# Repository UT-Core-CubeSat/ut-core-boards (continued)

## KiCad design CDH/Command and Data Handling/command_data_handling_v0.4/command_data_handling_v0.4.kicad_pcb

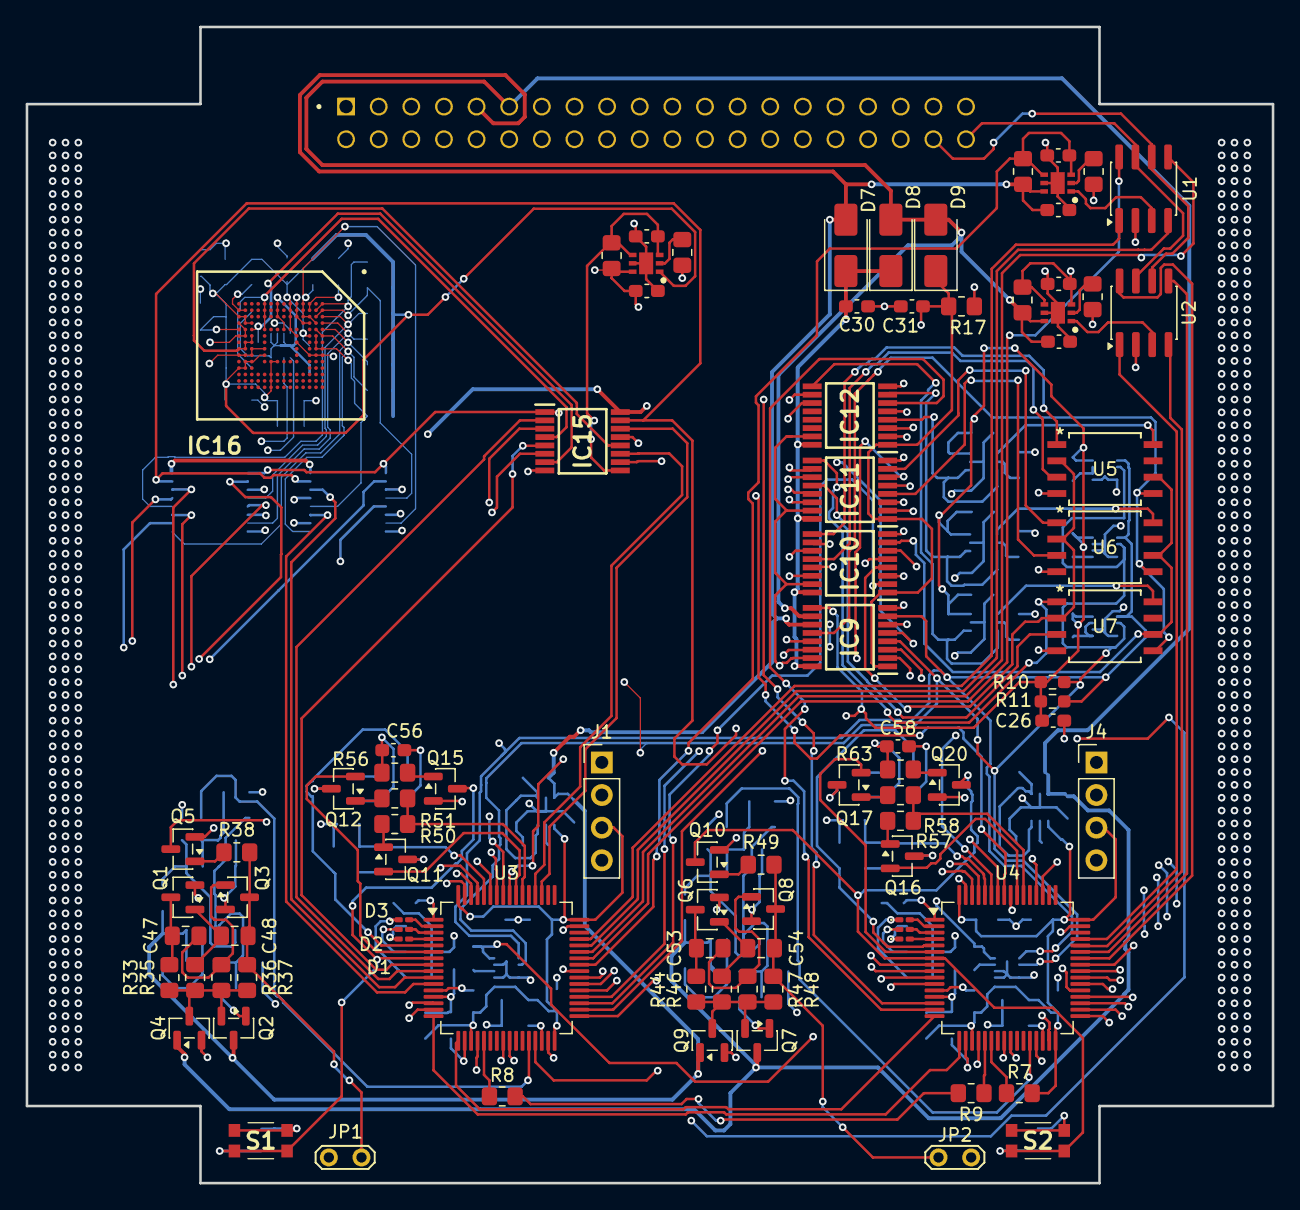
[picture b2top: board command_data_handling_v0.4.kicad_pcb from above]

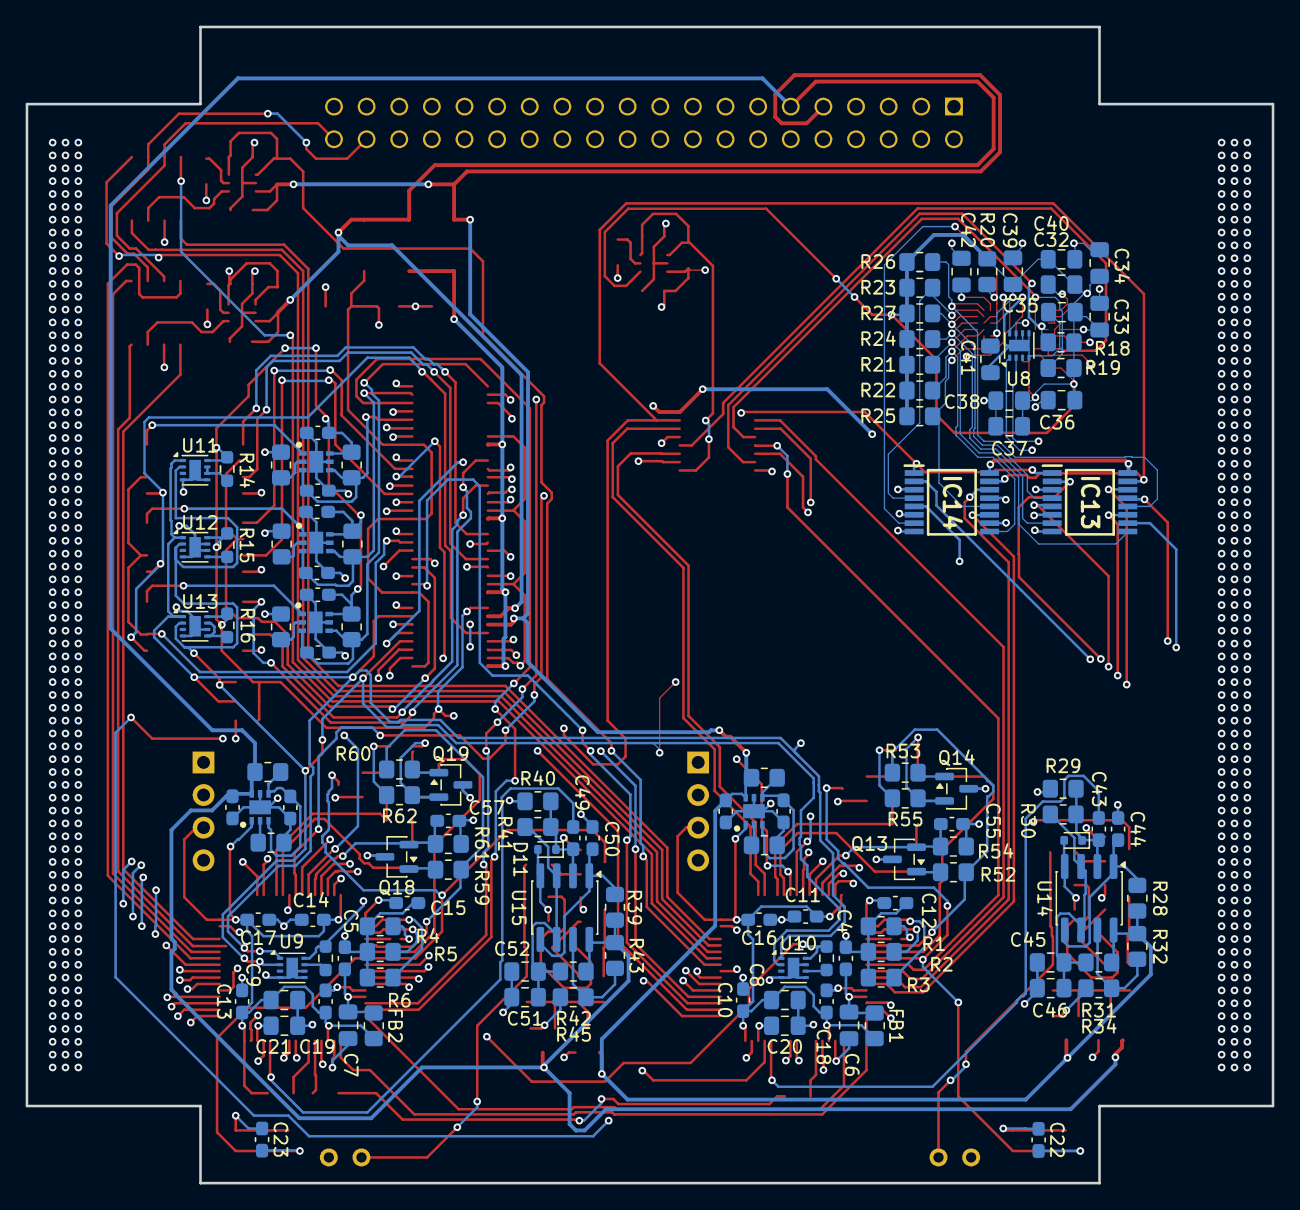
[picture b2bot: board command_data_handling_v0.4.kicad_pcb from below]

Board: 4 copper layers, 97.0 x 90.0 mm, 216 parts (125 on the bottom side), 196 nets.

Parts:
C1, C1_RETRY1, C2, C2_RETRY1, C3, C3_RETRY1, C4_RETRY1, C5_RETRY1, C6_RETRY1, C7_RETRY1, C7_RETRY2, C22, C23, C24, C25, C26, C27, C28, C29, C30, C31: 0.1µF; C_0603_1608Metric_Pad1.08x0.95mm_HandSolder
C4, C5, C10, C13, C16, C17, C18, C19, C43, C44, C49, C50: 100nF; C_0603_1608Metric_Pad1.08x0.95mm_HandSolder
C6, C7: 1µF; C_0805_2012Metric_Pad1.18x1.45mm_HandSolder
C8, C9: 10µF; C_0805_2012Metric_Pad1.18x1.45mm_HandSolder
C11, C12, C14, C15: 0.1μF; C_0603_1608Metric_Pad1.08x0.95mm_HandSolder
C20, C21, C32, C33, C34, C35, C36, C37, C38, C39, C40, C41, C42: 4.7µF; C_0805_2012Metric_Pad1.18x1.45mm_HandSolder
C45, C46, C51, C52: 10uF; C_0805_2012Metric_Pad1.18x1.45mm_HandSolder
C47, C48, C53, C54: 4.7uF; C_0805_2012Metric_Pad1.18x1.45mm_HandSolder
C55, C56, C57, C58: 0.1uF; C_0603_1608Metric_Pad1.08x0.95mm_HandSolder
D1, D2, D3, D4, D5, D6: LED; LED_0201_0603Metric_Pad0.64x0.40mm_HandSolder
D7, D8, D9: SS14; D_SMA
D10, D11: 1N4148; D_SOD-523
FB1, FB2: FerriteBead_Small; R_0805_2012Metric_Pad1.20x1.40mm_HandSolder
IC1, IC2, IC3, IC4, IC5, IC6, IC7, IC8: TPS2552DRVT-1
IC9, IC10, IC11, IC12, IC13, IC14, IC15: TMUX1574PWR
IC16: IS22EF08GP-JCLA2
J1, J4: SWD; PinHeader_1x04_P2.54mm_Vertical
J1#2: IPS1-120-01-L-D-RA
JP1, JP2: Jumper_2_Open; TestPoint_2Pads_Pitch2.54mm_Drill0.8mm
Q1, Q2, Q3, Q4, Q5, Q6, Q7, Q8, Q9, Q10, Q13, Q14, Q15, Q18, Q19, Q20: MMBT2222A; SOT-23
Q11, Q12, Q16, Q17: MMBTA94; SOT-23
R1, R2, R3, R4, R5, R6: 470Ω; R_0805_2012Metric_Pad1.20x1.40mm_HandSolder
R1_FAULT1, R2_FAULT1, R3_FAULT1, R4_FAULT1, R5_FAULT1, R6_FAULT1, R7_FAULT1, R7_FAULT2: 102kΩ; R_0805_2012Metric_Pad1.20x1.40mm_HandSolder
R1_ILIM1, R2_ILIM1, R3_ILIM1, R4_ILIM1: 88.7kΩ; R_0805_2012Metric_Pad1.20x1.40mm_HandSolder
R5_ILIM1, R6_ILIM1, R7_ILIM2: 226kΩ; R_0805_2012Metric_Pad1.20x1.40mm_HandSolder
R7, R8, R9, R33, R34, R37, R44, R45, R48: 1kΩ; R_0805_2012Metric_Pad1.20x1.40mm_HandSolder
R7_ILIM1: 108kΩ; R_0805_2012Metric_Pad1.20x1.40mm_HandSolder
R10, R11, R12, R13, R14, R15, R16: 5kΩ; R_0603_1608Metric_Pad0.98x0.95mm_HandSolder
R17, R28, R36, R38, R39, R47, R49, R56, R63: 100kΩ; R_0805_2012Metric_Pad1.20x1.40mm_HandSolder
R18: 4.7kΩ; R_0805_2012Metric_Pad1.20x1.40mm_HandSolder
R19, R29, R30, R31, R40, R41, R42, R50, R51, R52, R53, R57, R58, R59, R60: 10kΩ; R_0805_2012Metric_Pad1.20x1.40mm_HandSolder
R20, R21, R22, R23, R24, R25, R26, R27: 22.1kΩ; R_0805_2012Metric_Pad1.20x1.40mm_HandSolder
R32, R43, R54, R55, R61, R62: 5kΩ; R_0805_2012Metric_Pad1.20x1.40mm_HandSolder
R35, R46: 750kΩ; R_0805_2012Metric_Pad1.20x1.40mm_HandSolder
S1, S2: RESET; KMR731NGLFS
U1, U2: TCAN330; SOIC-8_3.9x4.9mm_P1.27mm
U3, U4: STM32U5A5RJTx; LQFP-64_10x10mm_P0.5mm
U5, U6, U7: CY15B104QN-50SXI
U8, U9, U10, U11, U12, U13: TMP1075DSG; WSON-8-1EP_2x2mm_P0.5mm_EP0.9x1.6mm
U14, U15: LM393; SOIC-8_3.9x4.9mm_P1.27mm

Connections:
/AND_Lock1/LCK1_1: R57.1, R58.1, U4.54 (PD2)
/AND_Lock1/LCK1_2: R59.2, R60.2, U4.5 (PH0)
/AND_Lock1/LCK1_OUT: C57.1, Q18.2 (E), R61.1, U4.60 (PH3)
/AND_Lock1/LCK2_IN: Q17.2 (E), U4.6 (PH1)
/AND_Lock/LCK1_1: R50.1, R51.1, U3.54 (PD2)
/AND_Lock/LCK1_2: R52.2, R53.2, U3.5 (PH0)
/AND_Lock/LCK1_OUT: C55.1, Q13.2 (E), R54.1, U3.60 (PH3)
/AND_Lock/LCK2_IN: Q12.2 (E), U3.6 (PH1)
/CANH: J1#2.40, U1.7 (CANH), U2.7 (CANH)
/CANL: J1#2.38, U1.6 (CANL), U2.6 (CANL)
/CDH1_3V3: C1.1, C24.1, D7.2 (A), IC2.6 (IN), IC4.6 (IN), IC9.11 (S3A), J1#2.09, Q2.3 (C), Q9.1 (B), R1_FAULT1.1, R2_FAULT1.2, R28.1, R31.2, R32.1, U14.8 (V+)
/CDH2_3V3: C2.1, C25.1, D8.2 (A), D9.2 (A), IC3.6 (IN), IC5.6 (IN), IC9.10 (S3B), J1#2.11, Q4.1 (B), Q7.3 (C), R3_FAULT1.1, R4_FAULT1.2, R39.1, R42.2, R43.1, U15.8 (V+)
/CLK: IC15.12 (D4), IC16.M6 (CLK), IC16.M7 (NC_81), IC16.N7 (NC_92), IC16.N8 (NC_93), IC16.P8 (NC_102)
/CMD: IC15.7 (D2), IC16.M5 (CMD), R18.1
/CS1: IC10.9 (D3), U5.1 (*CS)
/CS2: IC11.7 (D2), U6.1 (*CS)
/CS3: IC11.9 (D3), U7.1 (*CS)
/DAT0: IC13.4 (D1), IC16.A3 (DAT0), R27.1
/DAT1: IC13.7 (D2), IC16.A4 (DAT1), R24.1
/DAT2: IC13.9 (D3), IC16.A5 (DAT2), R21.1
/DAT3: IC13.12 (D4), IC16.A1 (NC_1), IC16.B2 (DAT3), R26.1
/DAT4: IC14.4 (D1), IC16.A2 (NC_2), IC16.B3 (DAT4), R23.1
/DAT5: IC14.7 (D2), IC16.B4 (DAT5), IC16.C3 (NC_20), IC16.D1 (NC_30), IC16.D2 (NC_31), IC16.D3 (NC_32), R20.1
/DAT6: IC14.9 (D3), IC16.A6 (VSS_1), IC16.B5 (DAT6), R22.1
/DAT7: IC14.12 (D4), IC16.A8 (NC_3), IC16.B6 (DAT7), IC16.B7 (NC_11), IC16.B8 (NC_12), R25.2
/EMMC_F: C7_RETRY1.1, IC1.3 (~FAULT), IC1.4 (EN), IC15.9 (D3), R7_FAULT1.1
/EMMC_VCC: C32.2, C33.2, C34.1, C35.2, C36.2, C37.2, C38.2, C39.2, C40.2, C41.2, IC1.1 (OUT), IC16.C6 (VCCQ_1), IC16.E6 (VCC_1), IC16.F1 (NC_43), IC16.F2 (NC_44), IC16.F3 (NC_45), IC16.F5 (VCC_2), IC16.H10 (VSS_4), IC16.J10 (VCC_3), IC16.J12 (NC_63), IC16.J13 (NC_64), IC16.J14 (NC_65), IC16.K9 (VCC_4), IC16.M4 (VCCQ_2), IC16.M10 (NC_84), IC16.N3 (NC_90), IC16.N4 (VCCQ_3), IC16.N10 (NC_95), IC16.N11 (NC_96), IC16.P3 (VCCQ_4), IC16.P5 (VCCQ_5), IC16.P11 (NC_104), R18.2, R19.2, R20.2, R21.2, R22.2, R23.2, R24.2, R25.1, R26.2, R27.2
/FRAM1_F: C5_RETRY1.1, IC6.3 (~FAULT), IC6.4 (EN), IC12.4 (D1), R5_FAULT1.1
/FRAM2_F: C6_RETRY1.1, IC7.3 (~FAULT), IC7.4 (EN), IC12.7 (D2), R6_FAULT1.1
/FRAM3_F: C7_RETRY2.1, IC8.3 (~FAULT), IC8.4 (EN), IC12.9 (D3), R7_FAULT2.1
/IC_I2C_SCL: IC9.4 (D1), R10.2, U8.2 (SCL), U9.2 (SCL), U10.2 (SCL), U11.2 (SCL), U12.2 (SCL), U13.2 (SCL)
/IC_I2C_SDA: IC9.7 (D2), R11.2, U8.1 (SDA), U9.1 (SDA), U10.1 (SDA), U11.1 (SDA), U12.1 (SDA), U13.1 (SDA)
/IC_SCK: IC10.7 (D2), U5.6 (SCK), U6.6 (SCK), U7.6 (SCK)
/IC_SI: IC9.12 (D4), U5.5 (SI), U6.5 (SI), U7.5 (SI)
/IC_SO: IC10.4 (D1), U5.2 (SO), U6.2 (SO), U7.2 (SO)
/MCU1_B0: Q11.2 (E), U3.55 (PB3)
/MCU1_CLK: IC15.14 (S4A), U3.51 (PC10)
/MCU1_CMD: IC15.5 (S2A), U3.8 (PC0)
/MCU1_CS1: IC10.11 (S3A), U3.29 (PB10)
/MCU1_CS2: IC11.5 (S2A), U3.61 (PB8)
/MCU1_CS3: IC11.11 (S3A), U3.56 (PB4)
/MCU1_DAT0: IC13.2 (S1A), U3.40 (PC9)
/MCU1_DAT1: IC13.5 (S2A), U3.39 (PC8)
/MCU1_DAT2: IC13.11 (S3A), U3.38 (PC7)
/MCU1_DAT3: IC13.14 (S4A), U3.37 (PC6)
/MCU1_DAT4: IC14.2 (S1A), U3.25 (PC5)
/MCU1_DAT5: IC14.5 (S2A), U3.24 (PC4)
/MCU1_DAT6: IC14.11 (S3A), U3.11 (PC3)
/MCU1_DAT7: IC14.14 (S4A), U3.10 (PC2)
/MCU1_EMMC_F: IC15.11 (S3A), U3.52 (PC11)
/MCU1_FRAM1_F: IC12.2 (S1A), U3.20 (PA4)
/MCU1_FRAM2_F: IC12.5 (S2A), U3.15 (PA1)
/MCU1_FRAM3_F: IC12.11 (S3A), U3.14 (PA0)
/MCU1_I2C1_SCL: IC9.2 (S1A), U3.58 (PB6)
/MCU1_I2C1_SDA: IC9.5 (S2A), U3.59 (PB7)
/MCU1_RST_N: IC15.2 (S1A), U3.9 (PC1)
/MCU1_SPI2_MISO: IC10.2 (S1A), U3.35 (PB14)
/MCU1_SPI2_MOSI: IC9.14 (S4A), U3.36 (PB15)
/MCU1_SPI2_SCK: IC10.5 (S2A), U3.34 (PB13)
/MCU1_WD: C43.1, U3.28 (PB2)
/MCU1_WP1: IC10.14 (S4A), U3.33 (PB12)
/MCU1_WP2: IC11.2 (S1A), U3.62 (PB9)
/MCU1_WP3: IC11.14 (S4A), U3.57 (PB5)
/MCU2_B0: Q16.2 (E), U4.55 (PB3)
/MCU2_CLK: IC15.13 (S4B), U4.51 (PC10)
/MCU2_CMD: IC15.6 (S2B), U4.8 (PC0)
/MCU2_CS1: IC10.10 (S3B), U4.29 (PB10)
/MCU2_CS2: IC11.6 (S2B), U4.61 (PB8)
/MCU2_CS3: IC11.10 (S3B), U4.56 (PB4)
/MCU2_DAT0: IC13.3 (S1B), U4.40 (PC9)
/MCU2_DAT1: IC13.6 (S2B), U4.39 (PC8)
/MCU2_DAT2: IC13.10 (S3B), U4.38 (PC7)
/MCU2_DAT3: IC13.13 (S4B), U4.37 (PC6)
/MCU2_DAT4: IC14.3 (S1B), U4.25 (PC5)
/MCU2_DAT5: IC14.6 (S2B), U4.24 (PC4)
/MCU2_DAT6: IC14.10 (S3B), U4.11 (PC3)
/MCU2_DAT7: IC14.13 (S4B), U4.10 (PC2)
/MCU2_EMMC_F: IC15.10 (S3B), U4.52 (PC11)
/MCU2_FRAM1_F: IC12.3 (S1B), U4.20 (PA4)
/MCU2_FRAM2_F: IC12.6 (S2B), U4.15 (PA1)
/MCU2_FRAM3_F: IC12.10 (S3B), U4.14 (PA0)
/MCU2_I2C1_SCL: IC9.3 (S1B), U4.58 (PB6)
/MCU2_I2C1_SDA: IC9.6 (S2B), U4.59 (PB7)
/MCU2_RST_N: IC15.3 (S1B), U4.9 (PC1)
/MCU2_SPI2_MISO: IC10.3 (S1B), U4.35 (PB14)
/MCU2_SPI2_MOSI: IC9.13 (S4B), U4.36 (PB15)
/MCU2_SPI2_SCK: IC10.6 (S2B), U4.34 (PB13)
/MCU2_WD: C49.1, U4.28 (PB2)
/MCU2_WP1: IC10.13 (S4B), U4.33 (PB12)
/MCU2_WP2: IC11.3 (S1B), U4.62 (PB9)
/MCU2_WP3: IC11.13 (S4B), U4.57 (PB5)
/MCU_MR: IC9.15 (~EN), IC10.15 (~EN), IC11.15 (~EN), IC12.15 (~EN), IC13.15 (~EN), IC14.15 (~EN), IC15.15 (~EN), R8.2, R9.2
/MUX_3V3: C3.1, C26.1, C27.1, C28.1, C29.1, IC1.6 (IN), IC6.6 (IN), IC7.6 (IN), IC8.6 (IN), IC9.9 (D3), R5_FAULT1.2, R6_FAULT1.2, R7_FAULT1.2, R7_FAULT2.2, R10.1, R11.1, R12.2, R13.2, R14.2, R15.2, R16.2, U8.8 (V+), U9.8 (V+), U10.8 (V+), U11.8 (V+), U12.8 (V+), U13.8 (V+)
/MUX_SEL: C31.2, D9.1 (K), IC9.1 (SEL), IC10.1 (SEL), IC11.1 (SEL), IC12.1 (SEL), IC13.1 (SEL), IC14.1 (SEL), IC15.1 (SEL), R17.2
/NRST1: C22.2, Q5.3 (C), Q15.3 (C), S1.1 (NO_1), S1.2 (NO_2), U3.7 (NRST)
/NRST2: C23.2, Q10.3 (C), Q20.3 (C), S2.1 (NO_1), S2.2 (NO_2), U4.7 (NRST)
/RST_N: IC15.4 (D1), IC16.K1 (NC_66), IC16.K2 (NC_67), IC16.K3 (NC_68), IC16.K5 (RST_N), R19.1
/USART2_1: U3.16 (PA2), U4.17 (PA3)
/USART2_2: U3.17 (PA3), U4.16 (PA2)
/VCC_MUX: C30.2, D7.1 (K), D8.1 (K), IC9.16 (VDD), IC10.16 (VDD), IC11.16 (VDD), IC12.16 (VDD), IC13.16 (VDD), IC14.16 (VDD), IC15.16 (VDD)
/VREF1: C8.1, C10.1, C11.1, C16.2, C18.1, FB1.2, IC2.1 (OUT), J1.3, U3.19 (VDD), U3.32 (VDD), U3.48 (VDDUSB), U3.64 (VDD)
/VREF2: C9.1, C13.1, C14.1, C17.2, C19.1, FB2.2, IC3.1 (OUT), J4.3, R7.2, U4.19 (VDD), U4.32 (VDD), U4.48 (VDDUSB), U4.64 (VDD)
/WP1: IC10.12 (D4), U5.3 (*WP)
/WP2: IC11.4 (D1), U6.3 (*WP)
/WP3: IC11.12 (D4), U7.3 (*WP)
/analog_watchdog1/Ref: C51.1, C52.1, R41.1, R42.1, U15.3 (+), U15.6 (-)
/analog_watchdog1/Ref2: C49.2, D11.1 (K), R40.1, R41.2, U15.2 (-)
/analog_watchdog/Ref: C45.1, C46.1, R30.1, R31.1, U14.3 (+), U14.6 (-)
/analog_watchdog/Ref2: C43.2, D10.1 (K), R29.1, R30.2, U14.2 (-)
GND: C1.2, C1_RETRY1.2, C2.2, C2_RETRY1.2, C3.2, C3_RETRY1.2, C4.2, C4_RETRY1.2, C5.2, C5_RETRY1.2, C6.2, C6_RETRY1.2, C7.2, C7_RETRY1.2, C7_RETRY2.2, C8.2, C9.2, C10.2, C11.2, C12.1, C13.2, C14.2, C15.1, C16.1, C17.1, C18.2, C19.2, C20.2, C21.2, C22.1, C23.1, C24.2, C25.2, C26.2, C27.2, C28.2, C29.2, C30.1, C31.1, C32.1, C33.1, C34.2, C35.1, C36.1, C37.1, C38.1, C39.1, C40.1, C41.1, C42.1, C44.2, C45.2, C46.2, C50.2, C51.2, C52.2, C55.2, C56.2, C57.2, C58.2, D10.2 (A), D11.2 (A), IC1.5 (GND), IC1.7 (EP), IC2.5 (GND), IC2.7 (EP), IC3.5 (GND), IC3.7 (EP), IC4.5 (GND), IC4.7 (EP), IC5.5 (GND), IC5.7 (EP), IC6.5 (GND), IC6.7 (EP), IC7.5 (GND), IC7.7 (EP), IC8.5 (GND), IC8.7 (EP), IC9.8 (GND), IC10.8 (GND), IC11.8 (GND), IC12.8 (GND), IC13.8 (GND), IC14.8 (GND), IC15.8 (GND), IC16.A9 (NC_4), IC16.B9 (NC_13), IC16.C4 (VSSQ_1), IC16.C9 (NC_24), IC16.D4 (NC_33), IC16.E1 (NC_37), IC16.E2 (NC_38), IC16.E3 (NC_39), IC16.E7 (VSS_2), IC16.G5 (VSS_3), IC16.H1 (NC_54), IC16.H2 (NC_55), IC16.H3 (NC_56), IC16.K8 (VSS_6), IC16.M8 (NC_82), IC16.M9 (NC_83), IC16.N2 (VSSQ_2), IC16.N5 (VSSQ_3), IC16.N6 (NC_91), IC16.N9 (NC_94), IC16.P2 (NC_101), IC16.P4 (VSSQ_4), IC16.P6 (VSSQ_5), IC16.P9 (NC_103), J1.4, J1#2.36, J4.4, JP1.1 (A), JP2.1 (A), Q1.2 (E), Q3.2 (E), Q4.2 (E), Q5.2 (E), Q6.2 (E), Q8.2 (E), Q9.2 (E), Q10.2 (E), Q15.2 (E), Q20.2 (E), R1.2, R1_ILIM1.2, R2.2, R2_ILIM1.2, R3.2, R3_ILIM1.2, R4.2, R4_ILIM1.2, R5.2, R5_ILIM1.2, R6.2, R6_ILIM1.2, R7_ILIM1.2, R7_ILIM2.2, R17.1, R29.2, R40.2, R54.2, R55.2, R61.2, R62.2, S1.3 (COM_1), S1.4 (COM_2), S2.3 (COM_1), S2.4 (COM_2), U1.2 (GND), U2.2 (GND), U3.12 (VSSA), U3.18 (VSS), U3.31 (VSS), U3.47 (VSS), U3.63 (VSS), U4.12 (VSSA), U4.18 (VSS), U4.31 (VSS), U4.47 (VSS), U4.63 (VSS), U5.4 (VSS), U6.4 (VSS), U7.4 (VSS), U8.4 (GND), U8.5 (A2), U8.6 (A1), U8.7 (A0), U8.9 (EP), U9.4 (GND), U9.5 (A2), U9.6 (A1), U9.9 (EP), U10.4 (GND), U10.5 (A2), U10.7 (A0), U10.9 (EP), U11.4 (GND), U11.5 (A2), U11.9 (EP), U12.4 (GND), U12.6 (A1), U12.7 (A0), U12.9 (EP), U13.4 (GND), U13.6 (A1), U13.9 (EP), U14.4 (V-), U15.4 (V-)
unnamed: D1.2 (A), U3.4 (PC15)
unnamed: D1.1 (K), R1.1
unnamed: D2.2 (A), U3.3 (PC14)
unnamed: D2.1 (K), R2.1
unnamed: D3.2 (A), U3.2 (PC13)
unnamed: D3.1 (K), R3.1
unnamed: D4.2 (A), U4.4 (PC15)
unnamed: D4.1 (K), R4.1
unnamed: D5.2 (A), U4.3 (PC14)
unnamed: D5.1 (K), R5.1
unnamed: D6.2 (A), U4.2 (PC13)
unnamed: D6.1 (K), R6.1
unnamed: IC1.2 (ILIM), R7_ILIM1.1
unnamed: C1_RETRY1.1, IC2.3 (~FAULT), IC2.4 (EN), R1_FAULT1.2
unnamed: IC2.2 (ILIM), R1_ILIM1.1
unnamed: C3_RETRY1.1, IC3.3 (~FAULT), IC3.4 (EN), R3_FAULT1.2
unnamed: IC3.2 (ILIM), R3_ILIM1.1
unnamed: C2_RETRY1.1, IC4.3 (~FAULT), IC4.4 (EN), R2_FAULT1.1, U3.41 (PA8)
unnamed: IC4.2 (ILIM), R2_ILIM1.1
unnamed: IC4.1 (OUT), U1.3 (VCC)
unnamed: C4_RETRY1.1, IC5.3 (~FAULT), IC5.4 (EN), R4_FAULT1.1, U4.41 (PA8)
unnamed: IC5.2 (ILIM), R4_ILIM1.1
unnamed: IC5.1 (OUT), U2.3 (VCC)
unnamed: IC6.2 (ILIM), R5_ILIM1.1
unnamed: IC6.1 (OUT), U5.8 (VDD)
unnamed: IC7.2 (ILIM), R6_ILIM1.1
unnamed: IC7.1 (OUT), U6.8 (VDD)
unnamed: IC8.2 (ILIM), R7_ILIM2.1
unnamed: IC8.1 (OUT), U7.8 (VDD)
unnamed: C42.2, IC16.C1 (NC_19), IC16.C2 (VDDI)
unnamed: C48.2, JP1.2 (B), Q3.3 (C), R37.2, R38.1
unnamed: C54.2, JP2.2 (B), Q8.3 (C), R48.2, R49.1
unnamed: C48.1, Q1.1 (B), R35.2
unnamed: C47.1, Q1.3 (C), R33.2
unnamed: Q2.1 (B), R34.2
unnamed: Q2.2 (E), Q4.3 (C), R33.1, R35.1, R36.1, R37.1
unnamed: C47.2, Q3.1 (B), R36.2
unnamed: Q5.1 (B), R38.2
unnamed: C54.1, Q6.1 (B), R46.2
unnamed: C53.1, Q6.3 (C), R44.2
unnamed: Q7.1 (B), R45.2
unnamed: Q7.2 (E), Q9.3 (C), R44.1, R46.1, R47.1, R48.1
unnamed: C53.2, Q8.1 (B), R47.2
unnamed: Q10.1 (B), R49.2
unnamed: Q11.1 (B), R50.2
unnamed: Q11.3 (C), Q13.3 (C)
unnamed: Q12.1 (B), R51.2
unnamed: Q12.3 (C), Q14.3 (C)
unnamed: Q13.1 (B), R52.1
unnamed: Q14.1 (B), R53.1
unnamed: C56.1, Q14.2 (E), R55.1, R56.1
unnamed: Q15.1 (B), R56.2
unnamed: Q16.1 (B), R57.2
unnamed: Q16.3 (C), Q18.3 (C)
unnamed: Q17.1 (B), R58.2
unnamed: Q17.3 (C), Q19.3 (C)
unnamed: Q18.1 (B), R59.1
unnamed: Q19.1 (B), R60.1
unnamed: C58.1, Q19.2 (E), R62.1, R63.1
unnamed: Q20.1 (B), R63.2
unnamed: R32.2, R34.1, U14.7
unnamed: R43.2, R45.1, U15.7
unnamed: U1.4 (RXD), U3.44 (PA11)
unnamed: U1.8 (S), U3.42 (PA9)
unnamed: U1.5 (SHDN), U3.43 (PA10)
unnamed: U1.1 (TXD), U3.45 (PA12)
unnamed: U2.4 (RXD), U4.44 (PA11)
unnamed: U2.8 (S), U4.42 (PA9)
unnamed: U2.5 (SHDN), U4.43 (PA10)
unnamed: U2.1 (TXD), U4.45 (PA12)
unnamed: R8.1, U3.21 (PA5)
unnamed: C12.2, U3.1 (VBAT)
unnamed: C20.1, U3.30 (VCAP)
unnamed: C4.1, C6.1, FB1.1, U3.13 (VDDA)
unnamed: R9.1, U4.21 (PA5)
unnamed: R7.1, U4.22 (PA6)
unnamed: C15.2, U4.1 (VBAT)
unnamed: C21.1, U4.30 (VCAP)
unnamed: C5.1, C7.1, FB2.1, U4.13 (VDDA)
unnamed: R12.1, U9.7 (A0)
unnamed: R13.1, U10.6 (A1)
unnamed: R14.1, U11.6 (A1), U11.7 (A0)
unnamed: R15.1, U12.5 (A2)
unnamed: R16.1, U13.5 (A2), U13.7 (A0)
unnamed: C44.1, R28.2, U14.1, U14.5 (+)
unnamed: C50.1, R39.2, U15.1, U15.5 (+)

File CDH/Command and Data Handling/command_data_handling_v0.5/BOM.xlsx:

Designator | Component | Model Number | Link | Quantity
U3,U4 | Micro Controller | STM32U5A5RJT6 | https://estore.st.com/en/stm32u5a5rjt6-cpn.html | 2
U1,U2 | Can Tranciever | TCAN3403-Q1 | https://www.mouser.com/ProductDetail/Texas-Instruments/TCAN3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 | 2
IC1,IC2,IC3,IC4,IC5,IC6,IC7,IC8 | Current Limiter | TPS2552DRVT-1 | https://www.digikey.com/en/products/detail/texas-instruments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 | 8
U8,U9,U10,U11,U12,U13 | Temperature Sensor | TMP1075 | https://www.digikey.com/en/products/detail/texas-instruments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 | 6
S1,S2 | Reset Button | KMR731NG LFS | https://www.mouser.com/ProductDetail/CK/KMR731NG-LFS?qs=uUke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 | 2
D7,D8,D9 | SS14 Shotky Diode | SS14-M3/61T | https://www.mouser.com/ProductDetail/Vishay-General-Semicond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 | 3
D10,D11 | Diode | 1N4148WT | https://www.digikey.com/en/products/detail/onsemi/1N4148WT/1954014 | 2
U14,U15 | Comparator | LM393BIDR | https://www.mouser.com/ProductDetail/Texas-Instruments/LM393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 | 2
U5,U6,U7 | FRAM | CY15B104QN-50SXI | https://www.digikey.com/en/products/detail/infineon-technolo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 | 3
J2,J3 | Pin Header | PEC05SFBN | https://www.digikey.com/en/products/detail/sullins-connector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 | 2
IC9,IC10,IC11,IC12,IC13,IC14,IC15 | Multiplexers | TMUX1574PWR | https://www.digikey.com/en/products/detail/texas-instruments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 | 7
Q1,Q2,Q3,Q4,Q5,Q6,Q7,Q8,Q9,Q10,Q13,Q14,Q15,Q18,Q19,Q20 | BJT NPN | MMBT2222A | https://www.mouser.com/ProductDetail/onsemi/MMBT2222ALT1G?qs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 | 16
Q11,Q12,Q16,Q17 | BJT PNP | MMBTA94 | https://www.mouser.com/ProductDetail/Diotec-Semiconductor/MM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 | 4
J1 | 40 Pin Connector | IPS1-120-01-L-D-RA | https://www.digikey.com/en/products/detail/samtec-inc/IPS1-1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 | 1
IC16 | EMMC | IS22EF08GP-JCLA2 | https://www.mouser.com/ProductDetail/ISSI/IS22EF08GP-JCLA2?q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 | 1
C1,C1_RETRY1,C2,C2_RETRY1,C3,C3_RETRY1,C4_RETRY1,C5_RETRY1,C6_RETRY1,C7_RETRY1,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 | 0.1 uF Capacitor | C0603X104J3RACAUTO | https://www.mouser.com/ProductDetail/KEMET/C0603X104J3RACAUT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 | 41
C6,C7 | 1 uF Capacitor | C0805X105J3RACAUTO | https://www.mouser.com/ProductDetail/KEMET/C0805X105J3RACAUT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 | 2
C20,C21,C32,C33,C34,C35,C36,C37,C38,C39,C40,C41,C42,C47,C48,C53,C54 | 4.7 uF Capacitor | C0805X475J3RACAUTO | https://www.mouser.com/ProductDetail/KEMET/C0805X475J3RACAUT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 | 17
C8,C9,C45,C46,C51,C52 | 10 uF Capacitor | C0805C106K8RACAUTO | https://www.mouser.com/ProductDetail/KEMET/C0805C106K8RACAUT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 | 6
R1,R2,R3,R4,R5,R6 | 470 resistor | RN73H2ATTD4700B25 | https://www.mouser.com/ProductDetail/KOA-Speer/RN73H2ATTD470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 | 6
R1_FAULT1,R2_FAULT1,R3_FAULT1,R4_FAULT1,R5_FAULT1,R6_FAULT1,R7_FAULT1,R7_FAULT2 | 102k resistor | RN73H2ATTD1023B25 | https://www.mouser.com/ProductDetail/KOA-Speer/RN73H2ATTD102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 | 8
R1_ILIM1,R2_ILIM1,R3_ILIM1,R4_ILIM1 | 88.7k resistor | RN73H2ATTD8872B25 | https://www.mouser.com/ProductDetail/KOA-Speer/RN73H2ATTD887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 | 4
R19,R29,R30,R31,R40,R41,R42,R50,R51,R52,R53,R57,R58,R59,R60 | 10k resistor | RN73H2ATTD1002B25 | https://www.mouser.com/ProductDetail/KOA-Speer/RN73H2ATTD100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 | 15
R7,R8,R9,R33,R34,R37,R44,R45,R48 | 1k resistor | RN73H2ATTD1001B25 | https://www.mouser.com/ProductDetail/KOA-Speer/RN73H2ATTD100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 | 9
R10,R11,R12,R13,R14,R15,R16,R32,R43,R54,R55,R61,R62 | 4.99k resistor | RN73H2ATTD4991B25 | https://www.mouser.com/ProductDetail/KOA-Speer/RN73H2ATTD499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 | 13
R17,R28,R36,R38,R39,R47,R49,R56,R63 | 100k resistor | RN73H2ATTD1003B25 | https://www.mouser.com/ProductDetail/KOA-Speer/RN73H2ATTD100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 | 9
R20,R21,R22,R23,R24,R25,R26,R27 | 22.1k resistor | RN73H2ATTD22R1B25 | https://www.mouser.com/ProductDetail/KOA-Speer/RN73H2ATTD22R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 | 8
R35,R46 | 750k resistor | RN73H2ATTD7503B25 | https://www.mouser.com/ProductDetail/KOA-Speer/RN73H2ATTD750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 | 2
R5_ILIM1,R6_ILIM1,R7_ILIM2 | 226k resistor | RN73H2ATTD2263B25 | https://www.mouser.com/ProductDetail/KOA-Speer/RN73H2ATTD226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 | 3
R7_ILIM1 | 109k resistor | RN73H2ATTD1093B25 | https://www.mouser.com/ProductDetail/KOA-Speer/RN73H2ATTD109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 | 1
FB1,FB2 | Ferrite Bead | 74279207 | https://www.mouser.com/ProductDetail/Wurth-Elektronik/742792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 | 2

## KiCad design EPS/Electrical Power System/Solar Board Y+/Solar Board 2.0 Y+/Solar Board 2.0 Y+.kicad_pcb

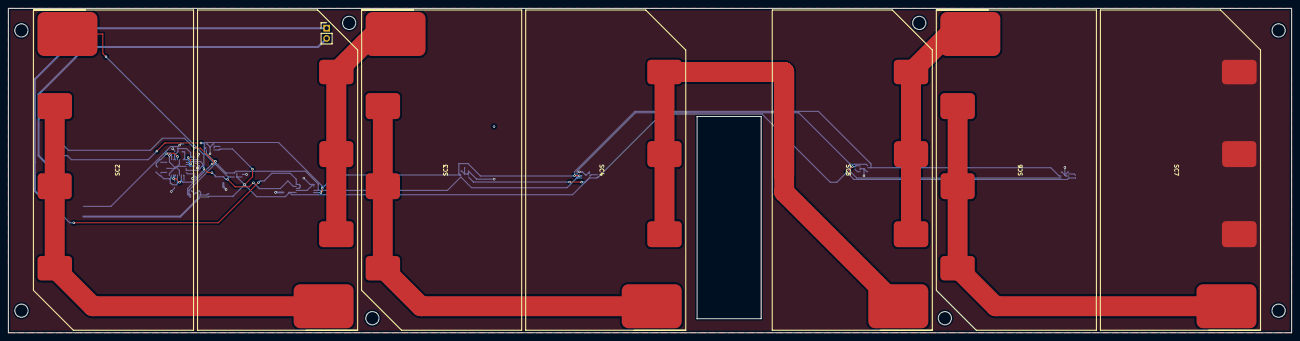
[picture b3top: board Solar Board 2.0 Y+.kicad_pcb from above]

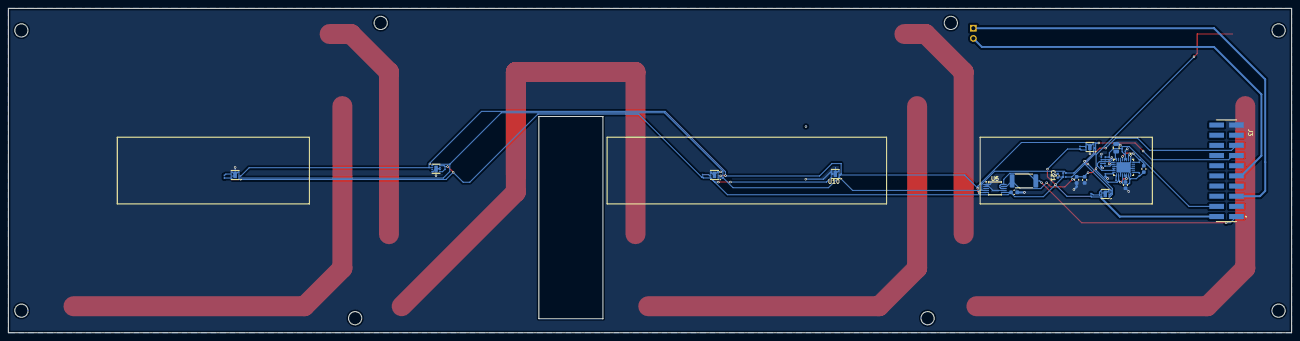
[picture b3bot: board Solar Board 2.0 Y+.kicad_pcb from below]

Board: 4 copper layers, 320.5 x 81.0 mm, 42 parts (34 on the bottom side), 29 nets.

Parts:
C1, C2: 100n; C_0603_1608Metric
C16: 10u; C_0603_1608Metric
C21: 0.01uF; C_0402_1005Metric
C50, C51: 0.1uF; C_0201_0603Metric
C52: 10uF; C_0201_0603Metric
C53: 22pF; C_0201_0603Metric
C54: 560pF; C_0201_0603Metric
C55: 10uF; C_0603_1608Metric
C56: 4.7uF; C_0805_2012Metric
J3: TSM-110-01-L-DV; 2x10 Pin Header
L50: 3.3uH; L_0603_1608Metric
M1: Motor_DC; PinHeader_1x02_P2.54mm_Vertical
R1, R2, R15, R16, R17, R18, R19: 5kΩ; R_0201_0603Metric
R50: 316k; R_0201_0603Metric
R51, R55: 100k; R_0201_0603Metric
R52: 39.2k; R_0201_0603Metric
R54: 200k; R_0201_0603Metric
R70: 0.1; R_2512_6332Metric
SC1, SC2, SC3, SC4, SC5, SC6, SC7: Solar_Cell
U5: INA226; VSSOP-10_3x3mm_P0.5mm
U7, U8, U9, U10, U11, U12: TMP1075DSG; WSON-8-1EP_2x2mm_P0.5mm_EP0.9x1.6mm
U50: LTC3119IUFD_PBF; LTC3119

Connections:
/3.3V_Batt: C2.1, C21.1, J3.02, R1.1, R2.1, R15.2, R16.2, R17.2, R18.2, R19.2, U5.6 (VS), U7.8 (V+), U8.8 (V+), U9.8 (V+), U10.8 (V+), U11.8 (V+), U12.8 (V+)
/3.3V_Solar: C52.1, C53.1, J3.04, R50.1, U50.3 (PVOUT), U50.4 (PVOUT__1)
/5V_BAT: J3.05, J3.09, M1.1 (+), M1.2 (-)
/IC_I2C_SCL: J3.13, R1.2, U5.5 (SCL), U7.2 (SCL), U8.2 (SCL), U9.2 (SCL), U10.2 (SCL), U11.2 (SCL), U12.2 (SCL)
/IC_I2C_SDA: J3.15, R2.2, U5.4 (SDA), U7.1 (SDA), U8.1 (SDA), U9.1 (SDA), U10.1 (SDA), U11.1 (SDA), U12.1 (SDA)
/VSOLAR_1: J3.01, R70.2, U5.8 (Vbus), U5.10 (Vin+)
/V_SOLAR: C1.1, C16.1, C55.1, R55.1, R70.1, SC2.1 (+), U5.9 (Vin-), U50.16 (VIN), U50.19 (PVIN), U50.20 (PVIN__1)
GND: C1.2, C2.2, C16.2, C21.2, C52.2, C54.2, C55.2, C56.2, J3.19, R51.2, R54.2, SC7.2 (-), U5.1 (A1), U5.2 (A0), U5.7 (GND), U7.4 (GND), U7.6 (A1), U7.9 (EP), U8.4 (GND), U8.5 (A2), U8.6 (A1), U8.9 (EP), U9.4 (GND), U9.5 (A2), U9.7 (A0), U9.9 (EP), U10.4 (GND), U10.5 (A2), U10.6 (A1), U10.7 (A0), U10.9 (EP), U11.4 (GND), U11.5 (A2), U11.9 (EP), U12.4 (GND), U12.6 (A1), U12.7 (A0), U12.9 (EP), U50.1 (PGND), U50.6 (PGND__1), U50.11 (SGND), U50.17 (PGND__2), U50.22 (PGND__3), U50.25 (PWM/SYNC), U50.29 (PGND__4)
unnamed: C54.1, R52.2
unnamed: SC1.1 (+), SC2.2 (-)
unnamed: SC1.2 (-), SC3.1 (+)
unnamed: SC3.2 (-), SC4.1 (+)
unnamed: SC4.2 (-), SC5.1 (+)
unnamed: SC5.2 (-), SC6.1 (+)
unnamed: SC6.2 (-), SC7.1 (+)
unnamed: R19.1, U7.5 (A2), U7.7 (A0)
unnamed: R15.1, U8.7 (A0)
unnamed: R16.1, U9.6 (A1)
unnamed: R17.1, U11.6 (A1), U11.7 (A0)
unnamed: R18.1, U12.5 (A2)
unnamed: C50.2, U50.23 (BST1)
unnamed: C51.2, U50.28 (BST2)
unnamed: C53.2, R50.2, R51.1, U50.9 (FB)
unnamed: C56.1, U50.8 (SVCC), U50.12 (MPPC), U50.13 (VCC)
unnamed: R54.1, U50.14 (RT)
unnamed: R55.2, U50.15 (RUN)
unnamed: C50.1, L50.1, U50.18 (SW1), U50.21 (SW1__1)
unnamed: C51.1, L50.2, U50.2 (SW2), U50.5 (SW2__1)
unnamed: R52.1, U50.10 (VC)
